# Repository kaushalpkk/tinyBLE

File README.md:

# tinyBLE
Bluetooth low energy breakout board based on the Nordic nRF8001 IC

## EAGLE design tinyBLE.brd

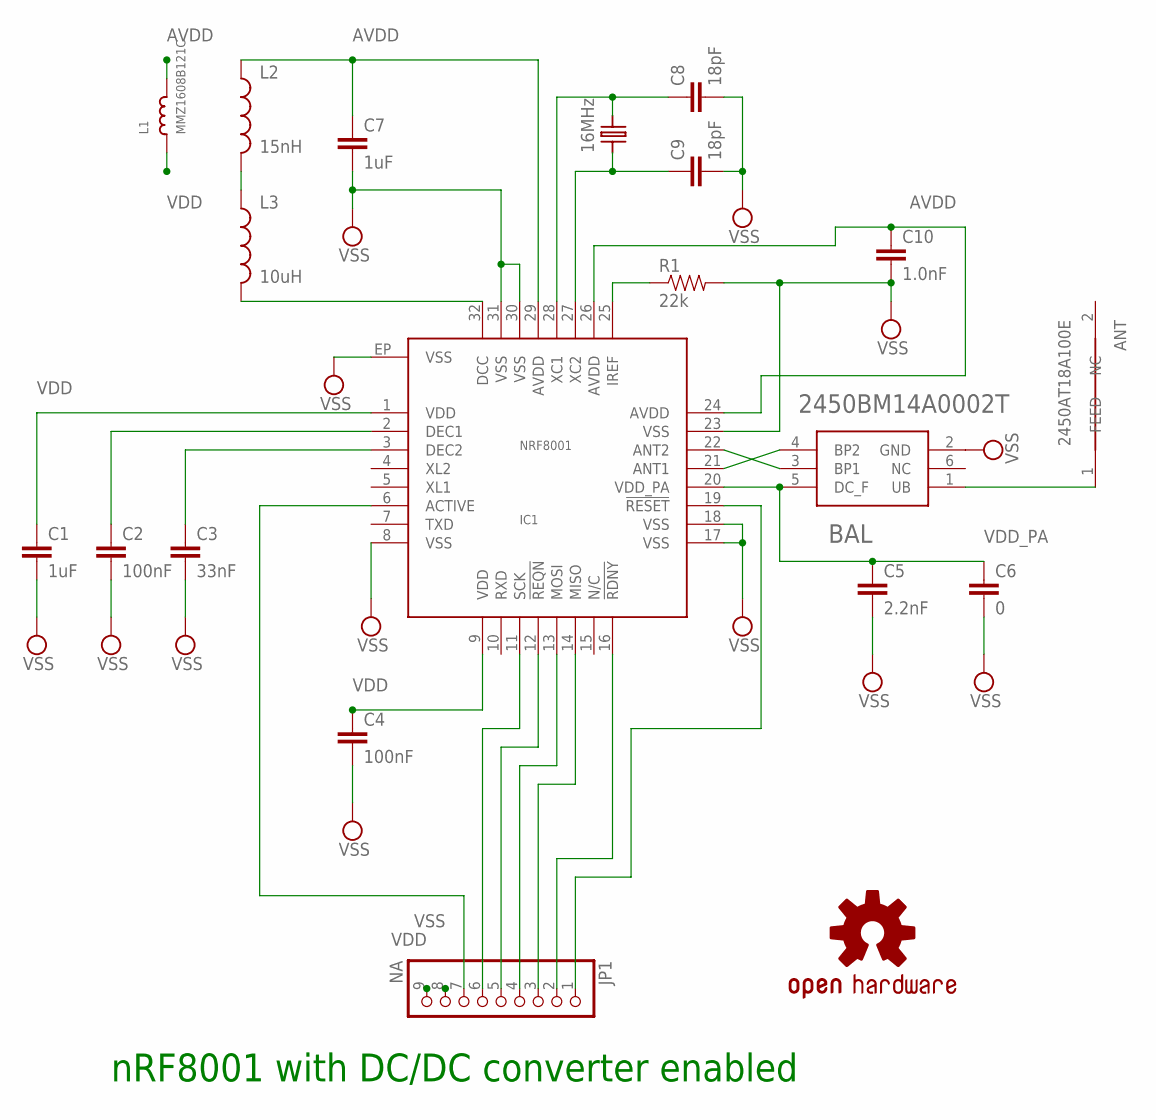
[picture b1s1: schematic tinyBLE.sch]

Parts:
ANT: 2450AT18A100E; ANT_0603
BAL: 2450BM14A0002T; BAL_0603
C1, C7: 1uF; 0603-CAP
C2, C4: 100nF; 0603-CAP
C3: 33nF; 0603-CAP
C5: 2.2nF; 0603-CAP
C6: 0; 0603-CAP
C8, C9: 18pF; 0603-CAP
C10: 1.0nF; 0603-CAP
IC1: NRF8001; QFN-32
JP1: NA; 1X09_OVAL
L1: MMZ1608B121C; 0603
L2: 15nH; 0603
L3: 10uH; 0603
LOGO1: OSHW-LOGOL; OSHW-LOGO-L
R1: 22k; 0603-RES
X1: 16MHz; CRYSTAL-2.5X3.5

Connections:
AVDD: C7.1, C10.1, IC1.24 (AVDD), IC1.26 (AVDD), IC1.29 (AVDD), L1.2, L2.1
unnamed: IC1.11 (SCK), JP1.6
unnamed: IC1.12 (!REQN), JP1.5
unnamed: IC1.13 (MOSI), JP1.4
unnamed: IC1.14 (MISO), JP1.3
unnamed: L2.2, L3.1
unnamed: IC1.32 (DCC), L3.2
unnamed: ANT.1 (FEED), BAL.1 (UB)
unnamed: C2.1, IC1.2 (DEC1)
unnamed: C3.1, IC1.3 (DEC2)
unnamed: BAL.3 (BP1), IC1.22 (ANT2)
unnamed: BAL.4 (BP2), IC1.21 (ANT1)
unnamed: IC1.25 (IREF), R1.1
unnamed: C9.1, IC1.27 (XC2), X1.P$1
unnamed: C8.1, IC1.28 (XC1), X1.P$3
NRF_ACTV: IC1.6 (ACTIVE), JP1.7
NRF_RDNY: IC1.16 (!RDNY), JP1.2
NRF_RST: IC1.19 (!RESET), JP1.1
VDD: C1.1, C4.1, IC1.1 (VDD), IC1.9 (VDD), JP1.9, L1.1
VDD_PA: BAL.5 (DC_F), C5.1, C6.1, IC1.20 (VDD_PA)
VSS: BAL.2 (GND), C1.2, C2.2, C3.2, C4.2, C5.2, C6.2, C7.2, C8.2, C9.2, C10.2, IC1.8 (VSS), IC1.17 (VSS), IC1.18 (VSS), IC1.23 (VSS), IC1.30 (VSS), IC1.31 (VSS), IC1.EP (VSS), JP1.8, R1.2

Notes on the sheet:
nRF8001 with DC/DC converter enabled

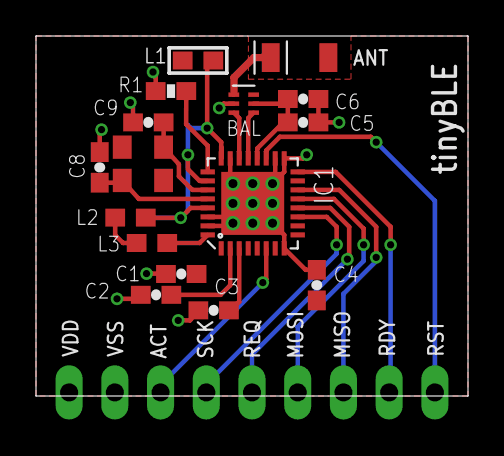
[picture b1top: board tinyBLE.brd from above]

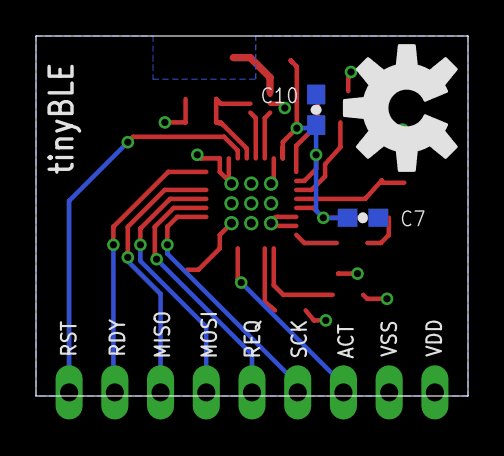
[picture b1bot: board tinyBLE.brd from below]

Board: 2 copper layers, 24.0 x 20.0 mm, 20 parts (3 on the bottom side), 21 nets.

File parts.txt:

Partlist

Exported from tinyBLE.sch at 06/02/2015 12:11:26

EAGLE Version 7.1.0 Copyright (c) 1988-2014 CadSoft

Assembly variant: 

Part     Value          Device           Package         Library       Sheet

ANT      2450AT18A100E  2450AT18A100E    ANT_0603        nrf51Lib_edit 1
BAL      2450BM14A0002T 2450BM14A0002T   BAL_0603        nrf51Lib_edit 1
C1       1uF            CAP0603-CAP      0603-CAP        SparkFun      1
C2       100nF          CAP0603-CAP      0603-CAP        SparkFun      1
C3       33nF           CAP0603-CAP      0603-CAP        SparkFun      1
C4       100nF          CAP0603-CAP      0603-CAP        SparkFun      1
C5       2.2nF          CAP0603-CAP      0603-CAP        SparkFun      1
C6       0              CAP0603-CAP      0603-CAP        SparkFun      1
C7       1uF            CAP0603-CAP      0603-CAP        SparkFun      1
C8       18pF           CAP0603-CAP      0603-CAP        SparkFun      1
C9       18pF           CAP0603-CAP      0603-CAP        SparkFun      1
C10      1.0nF          CAP0603-CAP      0603-CAP        SparkFun      1
IC1      NRF8001        NRF8001          QFN-32          FitnessDevice 1
JP1      NA             HEADER-1X9       1X09_OVAL       microbuilder  1
L1       MMZ1608B121C   INDUCTOR0603     0603            microbuilder  1
L2       15nH           INDUCTOR0603     0603            SparkFun      1
L3       10uF           INDUCTOR0603     0603            SparkFun      1
R12      22k            RESISTOR0603-RES 0603-RES        SparkFun      1
X1       16MHz          CRYSTAL-2.5X3.5  CRYSTAL-2.5X3.5 FitnessDevice 1

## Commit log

2015-02-13 initial Commit. updated Balun position for better harmonics.

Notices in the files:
parts and their libraries:
microbuilder: This work is placed in the public domain, and may be freely used for commercial and non-commercial work with the following conditions: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
SparkFun: Licensing: CC v3.0 Share-Alike You are welcome to use this library for commercial purposes.
